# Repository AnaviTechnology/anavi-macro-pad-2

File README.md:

# ANAVI Macro Pad 2

**Open source, programmable, two-key keypad with backlighting**

ANAVI Macro Pad 2 is an open source, custom-programmable, mini 2-key keyboard/keypad. Each key can be reprogrammed to activate a macro or even a dedicated shortcut - all without any coding experience! Powered by the advanced, but easy-to-use [Quantum Mechanical Keyboard (QMK) open source firmware](https://github.com/qmk/qmk_firmware/tree/master/keyboards/anavi/macropad8).

ANAVI Macro Pad 2 has been designed with [the cross platform and open source electronics design automation suite KiCad](https://kicad.org/). [The acrylic enclosure](https://github.com/AnaviTechnology/anavi-cases/tree/master/anavi-macro-pad-8-case) has been designed with [OpenSCAD](https://www.openscad.org/).

For more details please visit https://anavi.technology/

# License

The project is released under the [Creative Commons Attribution-ShareAlike 4.0 International (CC BY-SA 4.0)](https://creativecommons.org/licenses/by-sa/4.0/).

Note: This is a human-readable summary of (and not a substitute for) the [license](https://creativecommons.org/licenses/by-sa/4.0/legalcode).

You are free to:

Share — copy and redistribute the material in any medium or format Adapt — remix, transform, and build upon the material for any purpose, even commercially. The licensor cannot revoke these freedoms as long as you follow the license terms. Under the following terms:

Attribution — You must give appropriate credit, provide a link to the license, and indicate if changes were made. You may do so in any reasonable manner, but not in any way that suggests the licensor endorses you or your use. ShareAlike — If you remix, transform, or build upon the material, you must distribute your contributions under the same license as the original. No additional restrictions — You may not apply legal terms or technological measures that legally restrict others from doing anything the license permits. Notices:

You do not have to comply with the license for elements of the material in the public domain or where your use is permitted by an applicable exception or limitation. No warranties are given. The license may not give you all of the permissions necessary for your intended use. For example, other rights such as publicity, privacy, or moral rights may limit how you use the material.

You will have to provide a link to the original creator of the project http://www.anavi.technology on any documentation or website.

Credit can be attributed through a link to the creator website: http://www.anavi.technology

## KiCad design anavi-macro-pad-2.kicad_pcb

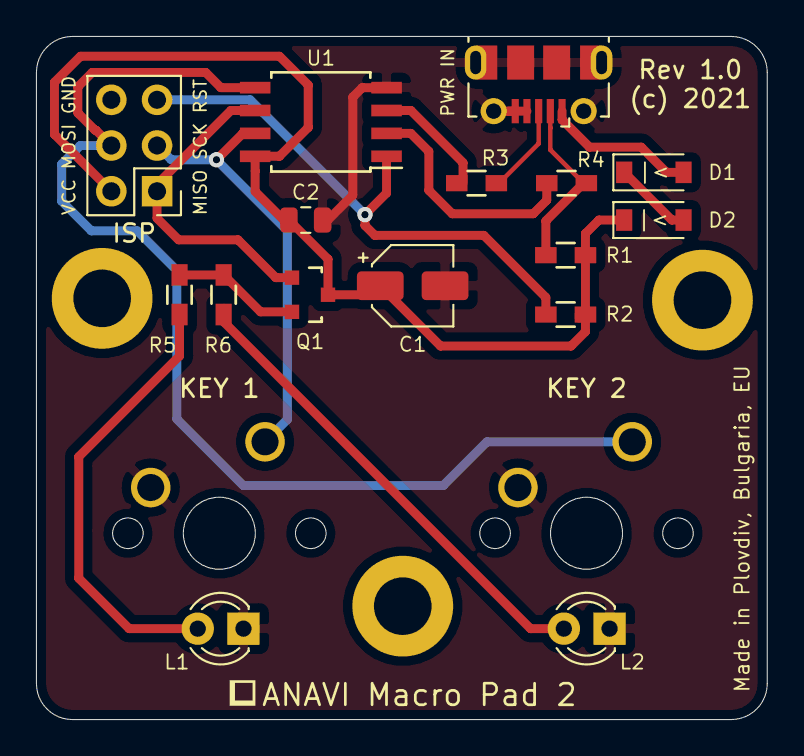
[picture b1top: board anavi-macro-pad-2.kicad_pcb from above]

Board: 2 copper layers, 40.6 x 38.0 mm, 18 parts (0 on the bottom side), 15 nets.

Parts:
C1: 10uF; CP_Elec_4x5.4
C2: 100nF; C_0805_2012Metric
D1, D2: 1N4148; D_SOD-123
ISP: AVR-ISP-6; PinHeader_2x03_P2.54mm_Vertical
J1: USB_B_Micro; USB_Micro-B_Molex-105017-0001
KEY 1, KEY 2: SW_DIP_x01; SW_Cherry_MX_1.00u_PCB
L1, L2: LED; LED_D3.0mm
Q1: Q_NPN_BEC; SOT-23
R1: 1.5K; R_0603_HandSoldering
R2: 10k; R_0603_HandSoldering
R3, R4: 22R; R_0603_HandSoldering
R5, R6: 68R; R_0603_HandSoldering
U1: ATtiny85-20SU; SOIJ-8_5.3x5.3mm_P1.27mm

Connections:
GND: C1.2, C2.2, ISP.6, J1.4, J1.5, J1.6, KEY 1.2, KEY 2.2, L1.1, L2.1, U1.4
unnamed: C1.1, C2.1, D2.1, ISP.2, Q1.3, R1.2, R2.1, U1.8
unnamed: D1.1, D2.2
unnamed: D1.2, J1.1
unnamed: J1.2, R1.1, R4.2
unnamed: J1.3, R3.2
unnamed: ISP.1, Q1.1, U1.6
unnamed: ISP.3, KEY 1.1, U1.7
unnamed: ISP.4, KEY 2.1, U1.5
unnamed: ISP.5, R2.2, U1.1
unnamed: L1.2, R5.1
unnamed: L2.2, R6.1
unnamed: Q1.2, R5.2, R6.2
unnamed: R3.1, U1.3
unnamed: R4.1, U1.2

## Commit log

2021-01-31 README.md: Initial commit
    Add README.md and .gitignore.
2021-01-31 Add KiCad project
    Add files for the KiCad project.
2021-01-31 anavi-macro-pad-2.kicad_pcb: Adjust label
    Adjust C2 label position.
2021-02-01 anavi-macro-pad-2.kicad_pcb: Minor adjustments
    Minor adjustments of the front silkscreen.
2021-02-07 anavi-macro-pad-2.kicad_pcb: Update silkscreen
    Update the silkscreen:
    - Replace 5V with VCC on the ISP connector because if measured
    when the board is booted from the microUSB it will be about
    3.6-3.7V because of diodes D1 and D2.
    - Remove the white frames around the keys
    - Replace labels K1 and K2 with KEY 1 and KEY 2
2021-02-07 bootloader/t85_default.hex: Micronucleus V2.04
    Add firmware binary for the open source bootloader for ATtiny85
    Micronucleus V2.04.
2021-10-31 README.md: Add anavi-macro-pad-2.jpg
    Add an image of ANAVI Macro Pad 2.
2024-02-06 README.md: Fix KiCad URL

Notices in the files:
anavi-macro-pad-2.kicad_pcb:
(c) 2021
